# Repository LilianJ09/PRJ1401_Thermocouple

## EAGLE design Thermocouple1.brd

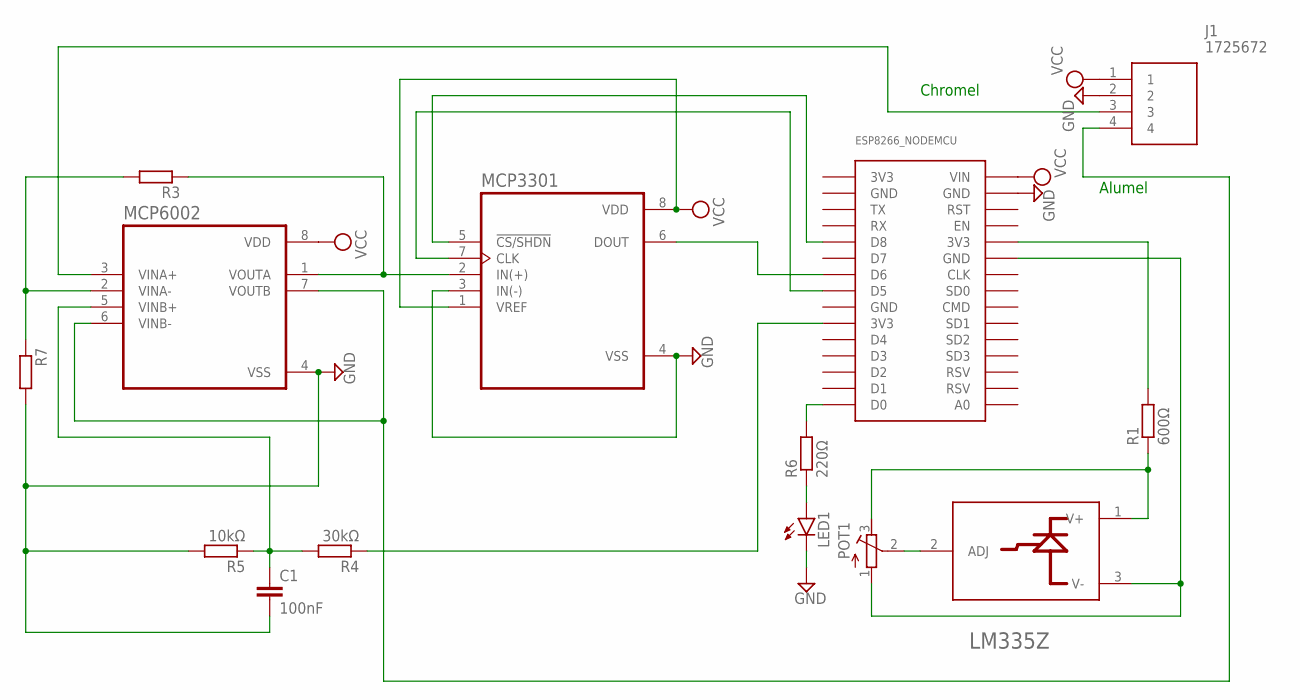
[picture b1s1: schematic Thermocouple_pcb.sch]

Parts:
C1: 100nF; C050-025X075
ESP8266_NODEMCU: NODEMCU_ESP8266
J1: 1725672; 1725672-4-2.54
LED1: LED5MM
LM335Z: STMICROELECTRONICS_LM335ZSTMICROELECTRONICS_LM335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; STMICROELECTRONICS_LM335Z_0
MCP3301: MCP3301-CI/P; DIP787W46P254L927H533Q8
MCP6002: MCP6002-I/P; DIP787W46P254L927H533Q8
POT1: R-TRIMM74W; RTRIM74W
R1: 600Ω; 0204/7
R3, R7: R-EU_0204/7; 0204/7
R4: 30kΩ; 0204/7
R5: 10kΩ; 0204/7
R6: 220Ω; 0204/7

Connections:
3V3: ESP8266_NODEMCU.3V3@1 (3V3)
GND: C1.2, ESP8266_NODEMCU.GND@1 (GND), ESP8266_NODEMCU.GND@2 (GND), ESP8266_NODEMCU.GND@4 (GND), J1.2, LED1.K (C), MCP3301.3 (IN(-)), MCP3301.4 (VSS), MCP6002.4 (VSS), R5.2, R7.2
unnamed: ESP8266_NODEMCU.D5, MCP3301.7 (CLK)
unnamed: ESP8266_NODEMCU.GND@3 (GND), LM335Z.3 (V-), POT1.1 (A)
unnamed: ESP8266_NODEMCU.D6, MCP3301.6 (DOUT)
unnamed: ESP8266_NODEMCU.D8, MCP3301.5 (!CS/SHDN)
unnamed: MCP3301.2 (IN(+)), MCP6002.1 (VOUTA), R3.1
unnamed: LED1.A, R6.1
unnamed: C1.1, MCP6002.5 (VINB+), R4.2, R5.1
unnamed: ESP8266_NODEMCU.3V3@3 (3V3), R1.2
unnamed: J1.3, MCP6002.3 (VINA+)
unnamed: LM335Z.1 (V+), POT1.3 (E), R1.1
unnamed: LM335Z.2 (ADJ), POT1.2 (S)
unnamed: J1.4, MCP6002.6 (VINB-), MCP6002.7 (VOUTB)
unnamed: ESP8266_NODEMCU.3V3@2 (3V3), R4.1
unnamed: MCP6002.2 (VINA-), R3.2, R7.1
unnamed: ESP8266_NODEMCU.D0, R6.2
VCC: ESP8266_NODEMCU.VIN, J1.1, MCP3301.1 (VREF), MCP3301.8 (VDD), MCP6002.8 (VDD)

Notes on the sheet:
Chromel
Alumel

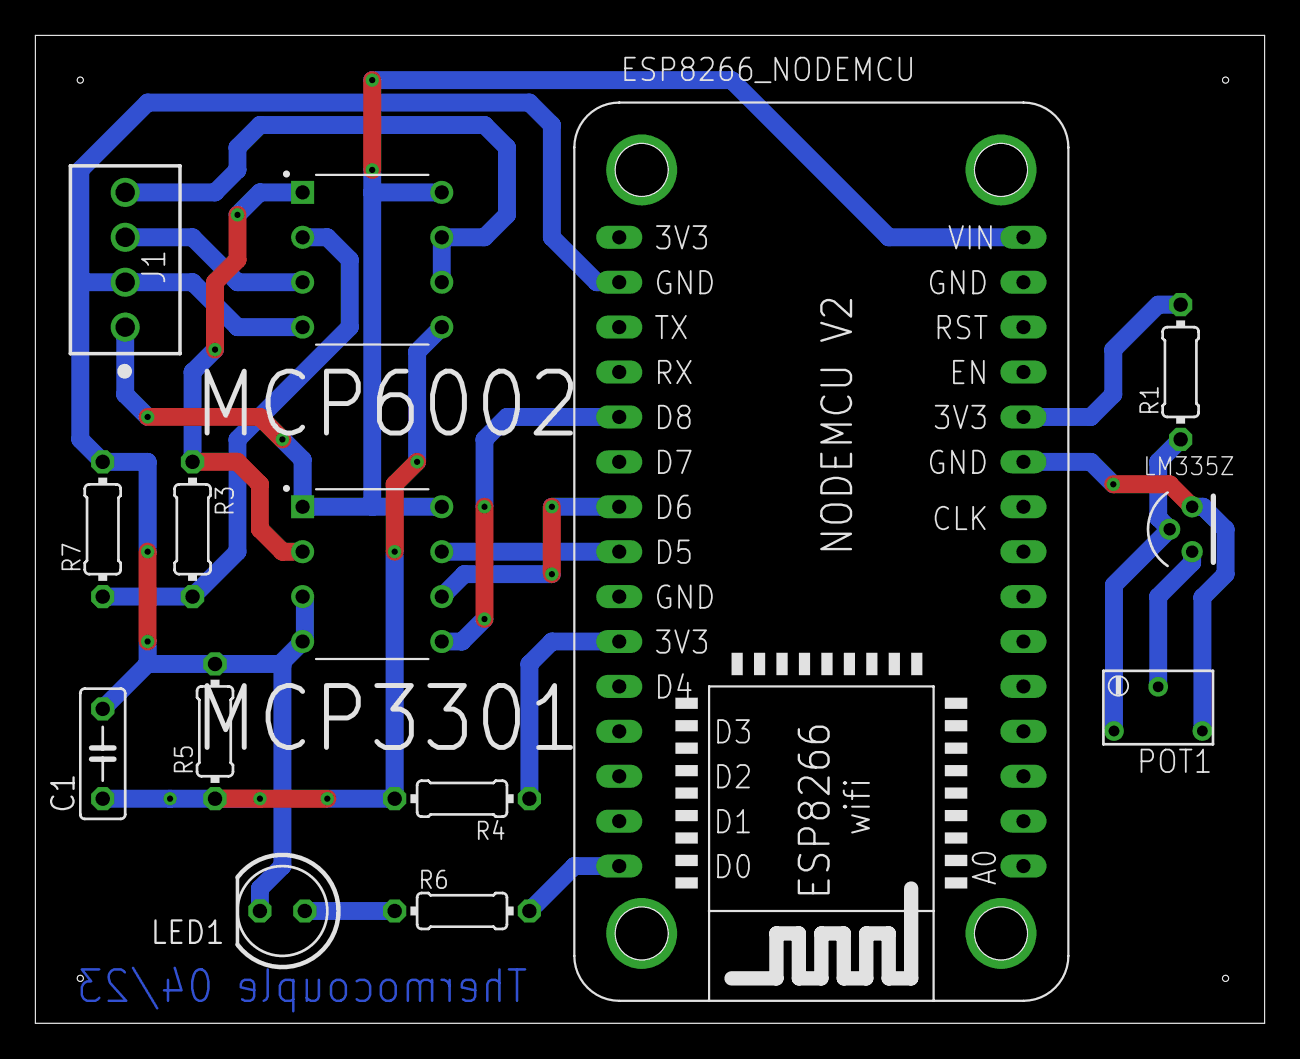
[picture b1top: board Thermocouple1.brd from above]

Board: 2 copper layers, 69.5 x 55.9 mm, 14 parts (0 on the bottom side), 17 nets.
